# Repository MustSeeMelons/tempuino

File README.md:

# Infrared temprature thing

Portable! Battery powered! Rechargable!

Programable with a generic FTDI module. It even has a cutout.

## Smol issue

Will not compile unless `.pio\libdeps\uno\ssd1306\src\ssd1306_hal\arduino\platform.cpp` is fixed by removing usages of `Wire1`. Just use `Wire` in their place. There was one more occurence.

## TODO

We might need to configure emissivity of the sensor. It defaults to 1.0.

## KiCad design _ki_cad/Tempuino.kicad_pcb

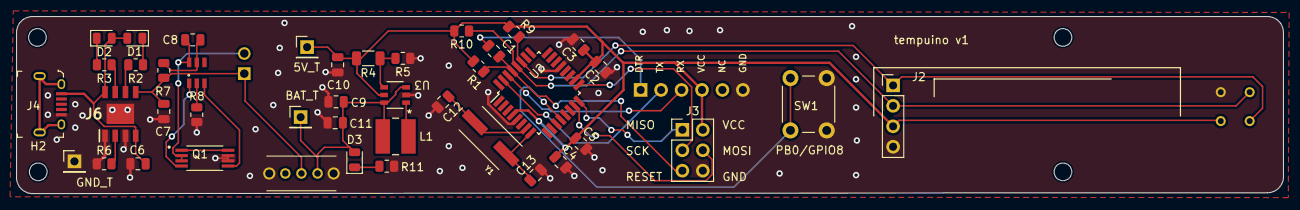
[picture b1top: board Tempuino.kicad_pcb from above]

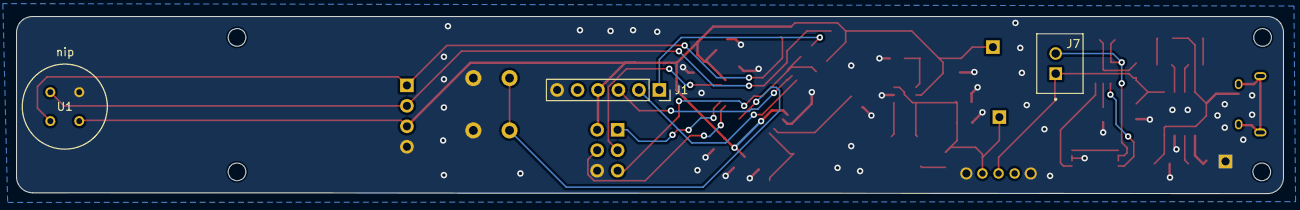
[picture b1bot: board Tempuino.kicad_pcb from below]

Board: 2 copper layers, 157.4 x 22.0 mm, 49 parts (3 on the bottom side), 30 nets.

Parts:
C1, C3, C4, C6, C8, C11: 100 nF; C_0805_2012Metric
C2, C5, C7, C9: 10 uF; C_0805_2012Metric
C10: 22 uF; C_0805_2012Metric
C12, C13: 20 pF; C_0805_2012Metric
D1, D2, D3: LED; LED_0805_2012Metric
H1, H2, H3, H4: MountingHole; MountingHole_2.2mm_M2
IC1: DW01A; SOT23-6
J1: Conn_01x06_Socket; PinSocket_1x06_P2.54mm_Vertical
J2: Conn_01x04_Pin; PinHeader_1x04_P2.54mm_Vertical
J3: Conn_02x03_Odd_Even; PinHeader_2x03_P2.54mm_Vertical
J4: 10118194-0001LF; USB_Micro_B_Female_10118194-0001LF
J5: GND_T; PinHeader_1x01_P2.54mm_Vertical
J6: TP4056; SOIC127P600X175-9N
J7: B2B-XH-A(LF)(SN); JST_B2B-XH-A(LF)(SN)
J8: B_T; PinHeader_1x01_P2.54mm_Vertical
J9: 5V_T; PinHeader_1x01_P2.54mm_Vertical
L1: 2.2 uH; IND_8357022_WRE
Q1: FS8205A; SOP65P640X120-8N
R1: 10K; R_0805_2012Metric
R2, R3, R6, R9, R10, R11: 1K; R_0805_2012Metric
R4: 900k Ohm; R_1206_3216Metric
R5: 100k Ohm; R_0805_2012Metric
R7: 100 Ohm; R_0805_2012Metric
R8: 1k Ohm; R_0805_2012Metric
SW1: SW_Push_Open; SW_PUSH_6mm
U1: MLX90614ESF-BCC-000-TU; MLX90614xCC_MEL
U2: ATmega328PB-A; TQFP-32_7x7mm_P0.8mm
U3: TLV61070ADBVR; SOT-23-6_DBV_TEX
U4: 1825232-1
Y1: ABLS7M-16.000MHZ-B-2-T; XTAL_ABLS7M-16.000MHZ-B-2-T

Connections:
/5V: C2.1, C3.1, C4.1, C5.1, C10.1, J1.4, J2.3, J3.2, J9.1, R1.2, R4.2, R9.2, R10.2, U1.3 (VDD), U2.4 (VCC), U2.18 (AVCC), U3.5 (VOUT)
/BAT_OUT: C9.1, C11.1, D3.2 (A), J8.1, L1.2, U3.3 (EN), U3.6 (VIN), U4.3
/CHARGE: J6.7 (~CHRG), R3.2
/DTR: C1.1, J1.1
/I2C_SCL: J2.2, R10.1, U1.1 (SCL/VZ), U2.28 (PC5)
/I2C_SDA: J2.1, R9.1, U1.2 (SDA/PWM), U2.27 (PC4)
/MISO_PB4: J3.1, U2.16 (PB4)
/MOSI_PB3: J3.4, U2.15 (PB3)
/PROG_SS: C1.2, J3.5, R1.1, U2.29 (~RESET/PC6)
/RX: J1.3, U2.30 (PD0)
/SCK_PB5: J3.3, U2.17 (PB5)
/STANDBY: J6.6 (~STDBY), R2.2
/TX: J1.2, U2.31 (PD1)
/VBUS: C6.1, D1.2 (A), D2.2 (A), J4.1, J6.4 (VCC4), J6.8 (CE)
GND: C2.2, C3.2, C4.2, C5.2, C6.2, C7.2, C9.2, C10.2, C11.2, C12.1, C13.2, J1.6, J2.4, J3.6, J4.5, J5.1, J6.1 (TEMP1), J6.3 (GND_3), J6.9 (EP), Q1.6, Q1.7, R5.1, R6.1, R8.1, R11.2, SW1.2 (B), U1.4 (VSS), U2.5 (GND), U2.21 (GND), U3.2 (GND), U4.GND, U4.GND1
unnamed: D1.1 (K), R2.1
unnamed: D2.1 (K), R3.1
unnamed: D3.1 (K), R11.1
unnamed: IC1.2 (CS), R8.2
unnamed: C8.2, IC1.6 (GND), J7.2, Q1.2, Q1.3
unnamed: IC1.3 (OC), Q1.5
unnamed: IC1.1 (OD), Q1.4
unnamed: C8.1, IC1.5 (VCC), R7.1
unnamed: C7.1, J6.5 (BAT), J7.1, R7.2, U4.2
unnamed: J6.2 (PROG2), R6.2
unnamed: SW1.1 (A), U2.12 (PB0)
unnamed: C12.2, U2.7 (XTAL1/PB6), Y1.2
unnamed: C13.1, U2.8 (XTAL2/PB7), Y1.1
unnamed: R4.1, R5.2, U3.4 (FB)
unnamed: L1.1, U3.1 (SW)

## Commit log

2024-04-01 Init
2024-05-15 Yeet Adafruit sensor lib
2024-06-12 Finished base funcionality
